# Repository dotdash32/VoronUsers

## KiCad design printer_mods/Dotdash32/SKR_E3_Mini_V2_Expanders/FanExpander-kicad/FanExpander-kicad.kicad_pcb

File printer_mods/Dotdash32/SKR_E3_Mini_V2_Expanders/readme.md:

# SKR E3 Mini V2.0 Expanders

A set of simple expander PCBs to give more thermistor and MOSFET fan outputs.

## Fan Expander

All fans have a 2 way voltage select header, and by moving a jumper between 5V and 24V (keeping the center Fx pin common), the drive voltage of the fan can easily be chosen.  If another voltage is desired for an individual fan, a jumper wire can also be tied directly into the Fx (center pin), providing any voltage higher than 5v.  All fans are broken out through JST-XH connectors.

All fans are also equipped with an indicator LED.  This LED is always driven from the 5V supply (EXP or external 5V supply pins) to ensure consistent brightness.  If you don't want the indicator LEDs, the jumper LED_EN can be cut to disable their power rail.  In a similar vein, if any fan is to be powered by less than 5V, the LED **must** be disabled at least for that fan, but is simplest to disable for the entire board by desoldering LED_EN.  

To keep all SMD components on one side (for manufacturing considerations), the LEDs shine through the board and into the connectors themselves.  This limits LED color options, but keeps the overall complexity and board size low.

### Fan Expander (Big Beefy Boi)

The "beefy boi" version of the Fan Expander uses either the EXP1 or EXP2 headers to drive up to 7 new fans and switch the voltage of one passthrough fan.  It can work next to a Thermistor Expander, or be mounted elsewhere and connected with a ribbon cable.

There are several "modes" of operation, mainly concerning voltage sources.  5V supply can come from the EXP header (EXP1 only), the 2 pin 5V header, or screw terminals.  24V (or other high voltage supply) can come from Fan0 In (passthrough fan) or the screw terminals.  Both supply lines are fused with ATM fuses, 3A standard, 10A optional.  See the [Operational_Modes.md](Operational_Modes.md) for detailed operation.

In general, JST-XH connectors are rated for 3A, and the BOM jumpers are specified to meet that current rating for each individual fan.  However, if using the Fan0 In connector, this limits the total current rating of the board.  Consider using the screw terminals for larger loads!

### Fan Expander Lite

The "Lite" version of the Fan Expander uses the EXP1 Header to drive 3 new fans and change the drive voltage for Fan1.  It is designed to be used next to the Thermistor Expander.  It is designed specifically for an SKR E3 in a Voron V0 (no external display, no SD card used).

Designed as a simpler, drop in solution than the fully featured Beefy Boi, it only has the LED_EN jumper and no others.  5V is supplied through EXP1, and 24V (or printer bus voltage) through Fan1 In connector.  Since it only uses 3 of 7 available I/O lines, so the remaining 4 lines are broken out to J7 IO Passthrough, next to a ground line each.

## Thermistor Expander

Uses SPI1 interface to add up to 3 thermistors on E3 based boards when an SD card is not needed.

Be aware, the SPI pins use 10k pull ups (next to SD-card on SKR board), which are different than the typical 4.7k pull ups.  This changes the thermistor sensitivity, so be aware they might not be as sensitive at printing temperatures.  This is based on Timmit's Umbilical mod, and the thermistor ports are designed for chamber and other low temperature and non-sensitive applications.

The TH4 Solder jumper switches the SPI pins that have been rearranged (V2.0 versus V3.0), and this solder jumper allows either SKR Mini E3 board to support 3 thermistors. All the pins are rearranged, so please see software configuration/schematic PDF for the correct pins for your board.

Klipper may try to read the SD card (which will fail, adding an RC circuit will destroy SPI timing requirements) during boot up if the thermistor pins are not declared as analog inputs, overriding their original SPI purpose.  Thus, please include the Thermistor Expander configuration before plugging the PCB in.  If your SKR refuses to boot, please unplug the Thermistor Expander PCB, boot up normally, then add the configuration file.

Requires 3 0805 SMD capacitors on the reverse side, which easier to source than THT variants (chip shortage, whoo), but are large enough to be relatively easy to hand solder.

## Bill of Materials

The BOM is shared between all sub-boards to make bulk ordering easier.

See the [Google Sheet](https://docs.google.com/spreadsheets/d/1q3EhH6Y6PAZSyFnE2HCBAoWyKbX_h1eaZGjsf7-CNqc/edit?usp=sharing).  Included is a "Composite Orderer" to allow a group order of all 3 sub assemblies to be ordered as one, as well as detailed BOMs for each.  This includes DigiKey alternatives to LCSC part numbers.

Each sub-project also has a csv file of it's specific BOM ready for import to LCSC included in this repository.  In each, JST-crimp connectors are also included, but can be excluded (since the larger wire gauge ones are sometimes difficult to source).  This saves some cost, but it's relatively small in the grand scheme of things.

## Errata

See the [Errata](Errata.md) for production issues and fixes.  While unfortunate, they must be documented.

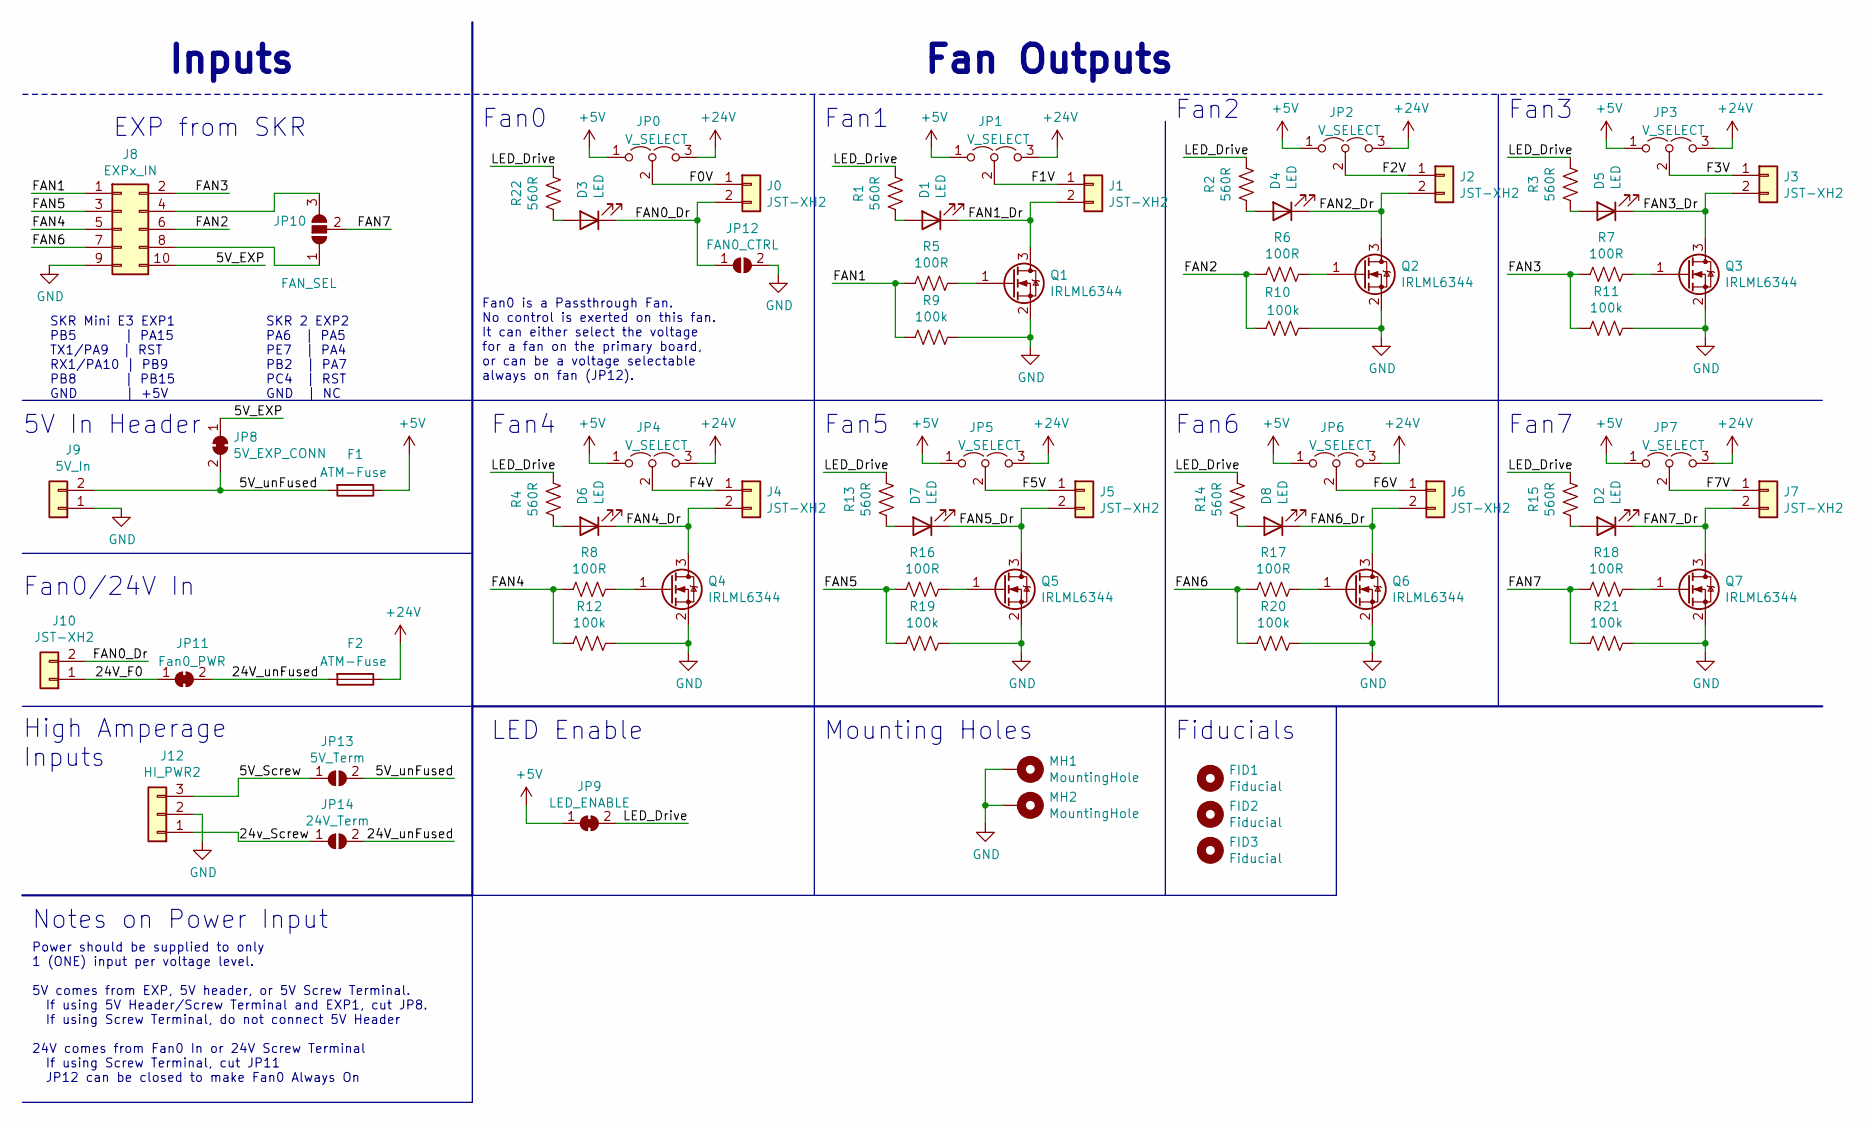
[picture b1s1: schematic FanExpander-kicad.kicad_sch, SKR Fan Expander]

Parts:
D1, D2, D3, D4, D5, D6, D7, D8: LED; LED_1206_3216Metric_ReverseMount_Hole2.1x2.1mm
F1, F2: ATM-Fuse; Fuseholder_Blade_Mini_Keystone_3544
FID1, FID2, FID3: Fiducial; Fiducial_0.5mm_Dia_1mm_Outer
J0, J1, J2, J3, J4, J5, J6, J7, J10: JST-XH2; JST_XH_B02B-XH-A_02x2.50mm_Straight
J8: EXPx_IN; Multicomp_MC9A12-1034_2x05x2.54mm_Straight
J9: 5V_In; Pin_Header_Straight_1x02_Pitch2.54mm
J12: HI_PWR2; TerminalBlock_Phoenix_MKDS-1,5-3-5.08_1x03_P5.08mm_Horizont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
JP0, JP1, JP2, JP3, JP4, JP5, JP6, JP7: V_SELECT; Pin_Header_Straight_1x03_Pitch2.54mm
JP8: 5V_EXP_CONN; SolderJumper-2_P1.3mm_Pasted_RoundedPad1.0x1.5mm
JP9: LED_ENABLE; SolderJumper-2_P1.3mm_Pasted_RoundedPad1.0x1.5mm
JP10: FAN_SEL; Pin_Header_Straight_1x03_Pitch1.27mm
JP11: Fan0_PWR; SolderJumper-2_P1.3mm_Pasted_RoundedPad1.0x1.5mm
JP12: FAN0_CTRL; SolderJumper-2_P1.3mm_Open_RoundedPad1.0x1.5mm
JP13: 5V_Term; SolderJumper-2_P1.3mm_Open_RoundedPad1.0x1.5mm
JP14: 24V_Term; SolderJumper-2_P1.3mm_Open_RoundedPad1.0x1.5mm
MH1, MH2: MountingHole; MountingHole_3.2mm_M3_Pad
Q1, Q2, Q3, Q4, Q5, Q6, Q7: IRLML6344; SOT-23
R1, R2, R3, R4, R13, R14, R15, R22: 560R; R_0603
R5, R6, R7, R8, R16, R17, R18: 100R; R_0603
R9, R10, R11, R12, R19, R20, R21: 100k; R_0603

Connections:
+5V: F1.1, JP0.1 (A), JP1.1 (A), JP2.1 (A), JP3.1 (A), JP4.1 (A), JP5.1 (A), JP6.1 (A), JP7.1 (A), JP9.1 (A)
+24V: F2.1, JP0.3 (B), JP1.3 (B), JP2.3 (B), JP3.3 (B), JP4.3 (B), JP5.3 (B), JP6.3 (B), JP7.3 (B)
/5V_EXP: J8.10, JP8.1 (A)
/5V_Screw: J12.3, JP13.1 (A)
/5V_unFused: F1.2, J9.2, JP8.2 (B), JP13.2 (B)
/24V_F0: J10.1, JP11.1 (A)
/24V_unFused: F2.2, JP11.2 (B), JP14.2 (B)
/24v_Screw: J12.1, JP14.1 (A)
/F0V: J0.1, JP0.2 (C)
/F1V: J1.1, JP1.2 (C)
/F2V: J2.1, JP2.2 (C)
/F3V: J3.1, JP3.2 (C)
/F4V: J4.1, JP4.2 (C)
/F5V: J5.1, JP5.2 (C)
/F6V: J6.1, JP6.2 (C)
/F7V: J7.1, JP7.2 (C)
/FAN0_Dr: D3.1 (K), J0.2, J10.2, JP12.1 (A)
/FAN1: J8.1, R5.2, R9.1
/FAN1_Dr: D1.1 (K), J1.2, Q1.3 (D)
/FAN2: J8.6, R6.2, R10.1
/FAN2_Dr: D4.1 (K), J2.2, Q2.3 (D)
/FAN3: J8.2, R7.2, R11.2
/FAN3_Dr: D5.1 (K), J3.2, Q3.3 (D)
/FAN4: J8.5, R8.2, R12.2
/FAN4_Dr: D6.1 (K), J4.2, Q4.3 (D)
/FAN5: J8.3, R16.2, R19.2
/FAN5_Dr: D7.1 (K), J5.2, Q5.3 (D)
/FAN6: J8.7, R17.2, R20.1
/FAN6_Dr: D8.1 (K), J6.2, Q6.3 (D)
/FAN7: JP10.2 (C), R18.2, R21.1
/FAN7_Dr: D2.1 (K), J7.2, Q7.3 (D)
/LED_Drive: JP9.2 (B), R1.2, R2.2, R3.2, R4.2, R13.2, R14.2, R15.2, R22.2
GND: J8.9, J9.1, J12.2, JP12.2 (B), MH1.1, MH2.1, Q1.2 (S), Q2.2 (S), Q3.2 (S), Q4.2 (S), Q5.2 (S), Q6.2 (S), Q7.2 (S), R9.2, R10.2, R11.1, R12.1, R19.1, R20.2, R21.2
unnamed: D1.2 (A), R1.1
unnamed: D2.2 (A), R15.1
unnamed: D3.2 (A), R22.1
unnamed: D4.2 (A), R2.1
unnamed: D5.2 (A), R3.1
unnamed: D6.2 (A), R4.1
unnamed: D7.2 (A), R13.1
unnamed: D8.2 (A), R14.1
unnamed: J8.4, JP10.3 (B)
unnamed: J8.8, JP10.1 (A)
unnamed: Q1.1 (G), R5.1
unnamed: Q2.1 (G), R6.1
unnamed: Q3.1 (G), R7.1
unnamed: Q4.1 (G), R8.1
unnamed: Q5.1 (G), R16.1
unnamed: Q6.1 (G), R17.1
unnamed: Q7.1 (G), R18.1

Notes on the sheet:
EXP from SKR
Fan1
Fan0 is a Passthrough Fan. No control is exerted on this fan. It can either select the voltage for a fan on the primary board, or can be a voltage selectable always on fan (JP12).
Fan0/24V In
Fan7
5V In Header
SKR 2 EXP2 PA6 | PA5 PE7 | PA4 PB2 | PA7 PC4 | RST GND | NC
Fan5
Mounting Holes
Notes on Power Input
Fan Outputs
LED Enable
Fan3
Fiducials
Fan0
SKR Mini E3 EXP1 PB5 | PA15 TX1/PA9 | RST RX1/PA10 | PB9 PB8 | PB15 GND | +5V
High Amperage Inputs
Fan4
Inputs
Fan6
Fan2
Power should be supplied to only 1 (ONE) input per voltage level. 5V comes from EXP, 5V header, or 5V Screw Terminal. If using 5V Header/Screw Terminal and EXP1, cut JP8. If using Screw Terminal, do not connect 5V Header 24V comes from Fan0 In or 24V Screw Terminal If using Screw Terminal, cut JP11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

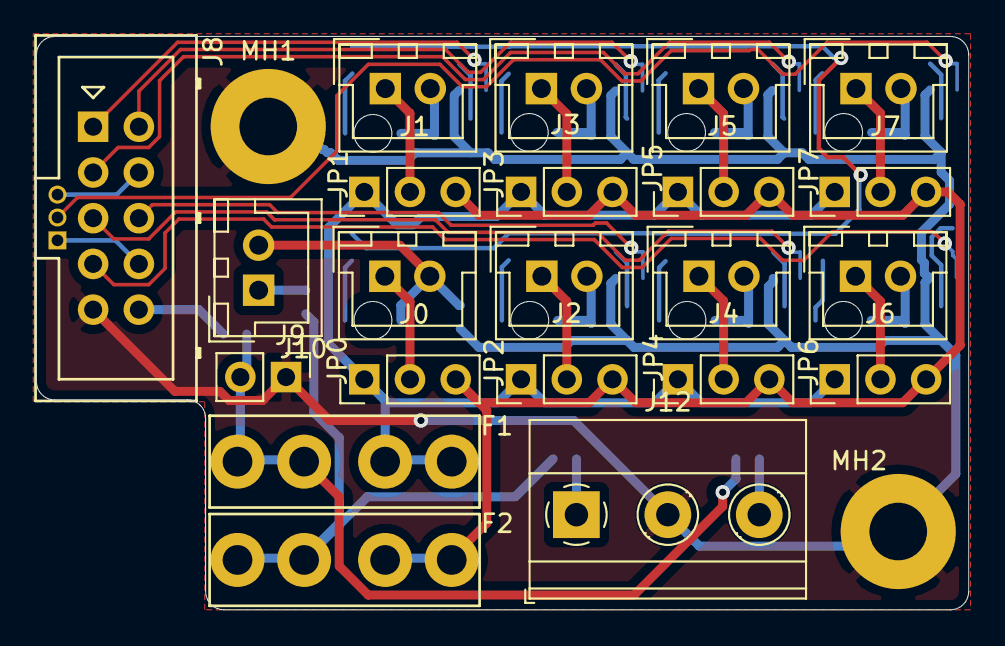
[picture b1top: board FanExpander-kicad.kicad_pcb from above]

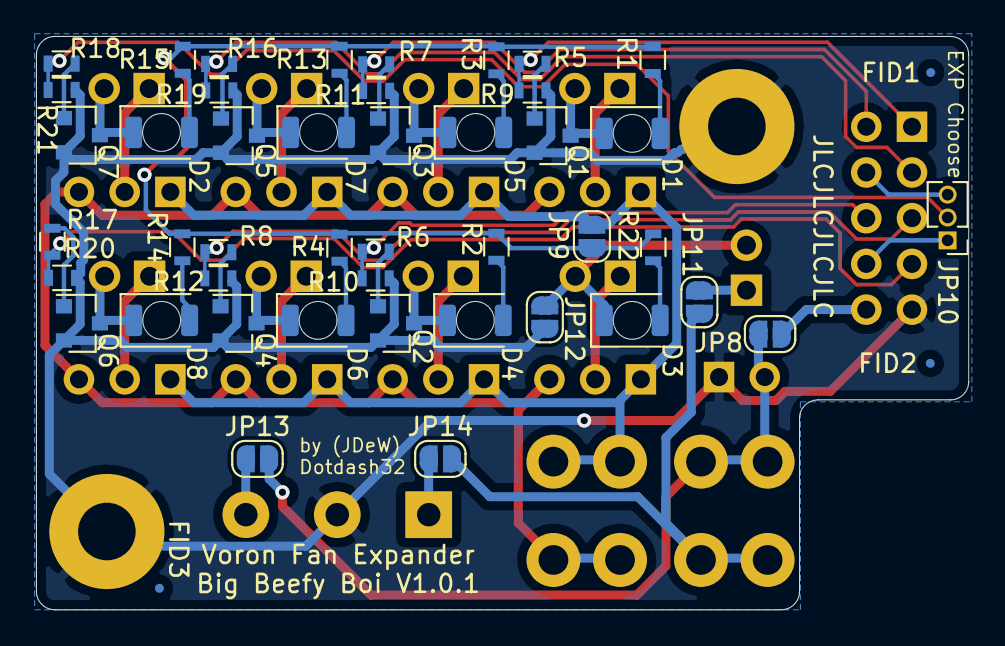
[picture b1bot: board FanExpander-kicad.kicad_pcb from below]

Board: 2 copper layers, 51.8 x 31.9 mm, 71 parts (47 on the bottom side), 50 nets.

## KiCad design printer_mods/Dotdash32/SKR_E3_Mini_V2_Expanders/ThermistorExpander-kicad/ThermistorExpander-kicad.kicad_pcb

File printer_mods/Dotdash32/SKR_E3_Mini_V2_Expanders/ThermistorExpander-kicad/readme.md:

# Thermistor Expander

This PCB is probably not supremely useful, but it has a special place in my heart.

Here are some pretty pictures of what it looks like!

## Images

### Bill of Materials

See the Google Doc linked on the main page

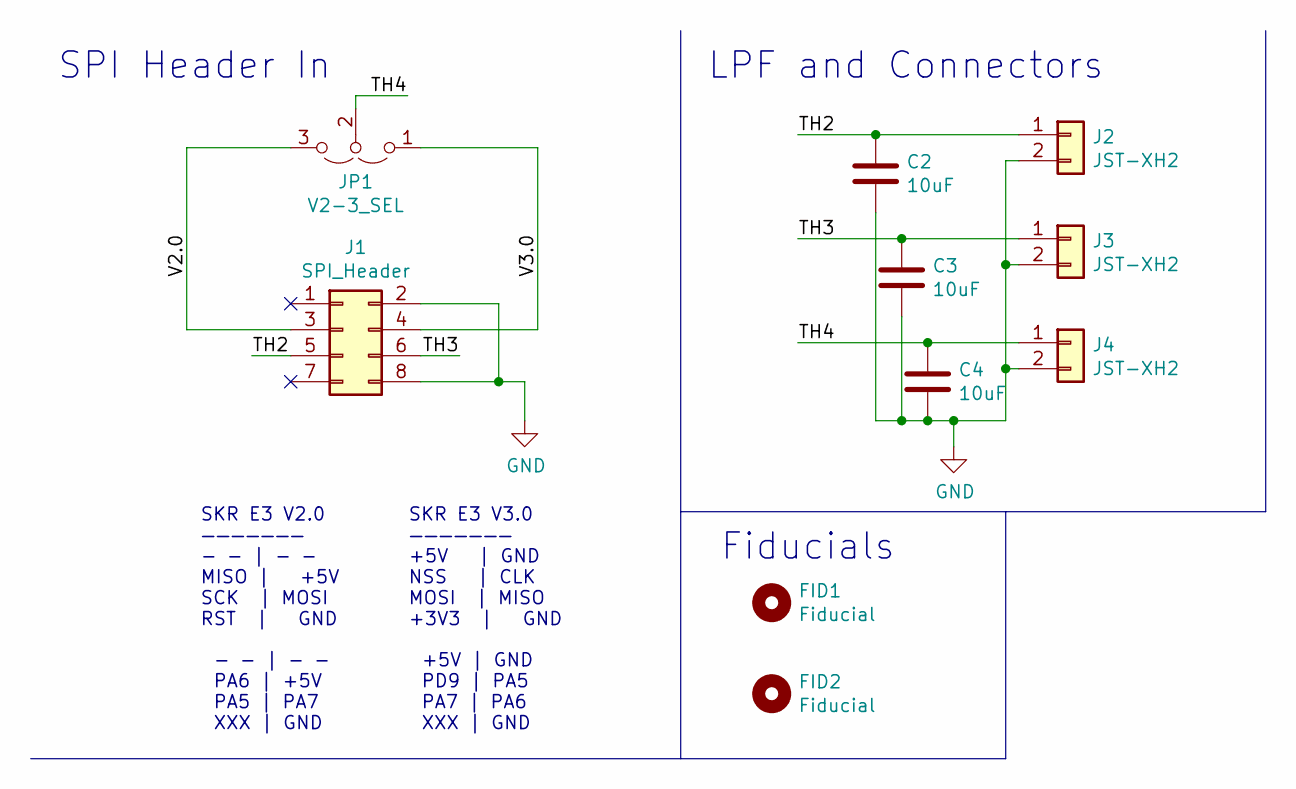
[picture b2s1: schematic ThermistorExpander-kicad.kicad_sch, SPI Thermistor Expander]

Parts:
C2, C3, C4: 10uF; C_0805_HandSoldering
FID1, FID2: Fiducial; Fiducial_0.5mm_Dia_1mm_Outer
J1: SPI_Header; Pin_Header_Straight_2x04_Pitch2.54mm
J2, J3, J4: JST-XH2; JST_XH_B02B-XH-A_02x2.50mm_Straight
JP1: V2-3_SEL; SolderJumper-3_P1.3mm_Open_Pad1.0x1.5mm

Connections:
/TH2: C2.1, J1.5, J2.1
/TH3: C3.1, J1.6, J3.1
/TH4: C4.1, J4.1, JP1.2 (C)
/V2.0: J1.3, JP1.3 (B)
/V3.0: J1.4, JP1.1 (A)
GND: C2.2, C3.2, C4.2, J1.2, J1.8, J2.2, J3.2, J4.2

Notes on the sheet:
- - | - - PA6 | +5V PA5 | PA7 XXX | GND
SPI Header In
LPF and Connectors
SKR E3 V2.0 ——————— - - | - - MISO | +5V SCK | MOSI RST | GND
Fiducials
+5V | GND PD9 | PA5 PA7 | PA6 XXX | GND
SKR E3 V3.0 ——————— +5V | GND NSS | CLK MOSI | MISO +3V3 | GND

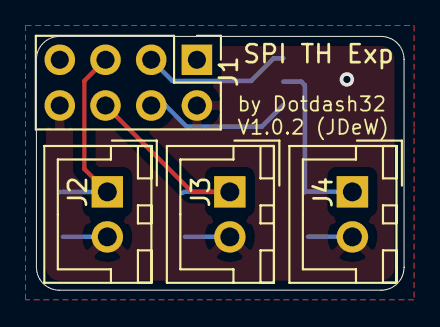
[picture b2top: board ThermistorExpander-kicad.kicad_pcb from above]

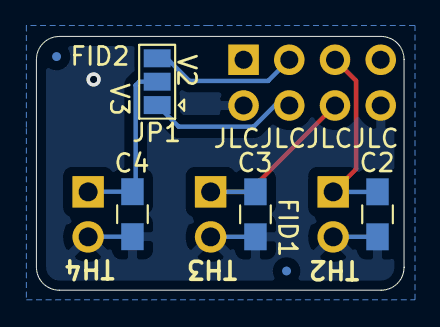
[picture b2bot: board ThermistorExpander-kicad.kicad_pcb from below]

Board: 2 copper layers, 20.4 x 14.1 mm, 10 parts (6 on the bottom side), 6 nets.

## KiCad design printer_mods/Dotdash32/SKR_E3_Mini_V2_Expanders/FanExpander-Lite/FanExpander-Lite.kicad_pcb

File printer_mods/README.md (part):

# Mods

Printer mods for Voron 3D printers
Remember to update this README when uploading new mod!

## Legacy printers

Mods for legacy printers can be found [here](../legacy_printers/printer_mods).
If one of your mods applies to a current generation Voron printer, contact the admins in
Discord to have your mod moved to this folder.

## Table structure

Update the following table with the information about your mod:
- Your name
- A link to your sub-folder
- A short description of your mod
- The printer compatibility. Use `:heavy_check_mark:` for :heavy_check_mark:,`:x:` for :x: and `:grey_question:` for :grey_question:

like so:
`
| Creator | [Mod title](link) | Description | :x: | :x: | :x: | :x: | :x:|`

---

| Creator | Mod title | Description | V0 | V1.8 | V2.4 | VSW | Trident |
| --- | --- | --- | --- | --- | --- | --- | --- |
|120decibell|[Side entry exhaust housing](./120decibell/exhaust_housing_side_entry)| Exhaust housing with dual cover screws and single or dual side entry filament paths. |:x:|:heavy_check_mark:|:heavy_check_mark:|:x:|:heavy_check_mark:|
||[Huvud Chain Mount](./120decibell/huvud_chain_mount)| Huvud rear mount for Clockwork or LGX that supports a cable chain. |:x:|:heavy_check_mark:|:grey_question:|:x:|:heavy_check_mark:|
|42bios|[Corner panel clip w. cable](./42bios/corner_panel_clip_cable)| Corner panel clip with an internal cable path. |:x:|:grey_question:|:heavy_check_mark:|:x:|
| |[Exhaust filter housing - side thread](./42bios/exhaust_filter_housing_side)|Exhaust filter housing with the G1-8 "thread on the side. |:x:|:grey_question:|:heavy_check_mark:|:x:|
| |[LED mount](./42bios/LED_mount)|AngryLED - LED-mount for Lumentech LT3 profiles. |:x:|:grey_question:|:heavy_check_mark:|:x:|
| |[relay mount](./42bios/relay_mount)|relay-mount for 2x 2 channel relay modules.|:x:|:grey_question:|:heavy_check_mark:|:x:|
|aeresov|[TL filament sensor bracket](./aeresov/TL_filament_sensor_bracket)|A bracket for TL filament sensor to mount near stock spool holder. |:x:|:grey_question:|:heavy_check_mark:|:x:|
||[MeanWell UHP-xxx DIN mount](./aeresov/MeanWell_UHP_DIN_mount)|A bracket for MeanWell UHP series PSU (200, 350 and 500) to mount it across 2 DIN rails.|:x:|:grey_question:|:heavy_check_mark:|
||[Raspberry Pi DIN mount](./aeresov/Raspberry_Pi_DIN_mount)|A bracket for Raspberry Pi 3/4 to mount it onto DIN rail, along or across.|:x:|:grey_question:|:heavy_check_mark:|
||[SKR 1.3/1.4 DIN mount](./aeresov/SKR_DIN_mount)|A bracket for SKR 1.3/1.4 board to mount it onto DIN rail, along or across.|:x:|:grey_question:|:heavy_check_mark:|
||[cable tie DIN mount](./aeresov/cable_tie_DIN_mount)|A bracket for cable ties to route cables across DIN rails.|:x:|:grey_question:|:heavy_check_mark:|
|alanho|[BTT PITFT50 v2 Mount](./alanho/BTT_PITFT50_v2_Mount)|A mount for the BTT PITFT50 v2 Touch Display |:x:|:grey_question:|:heavy_check_mark:|:x:|
|albert|[IKEA Dioder Led Mount](./albert/IKEA_Dioder_Led_Mount)|A mount for the IKEA Dioder LED strip | :grey_question: | :grey_question: | :heavy_check_mark: |:x:|
|al3ph|[LED Mount](./al3ph/led_mount)|A mount for 10mm LED WS2812 strips |:heavy_check_mark:|:x:|:x:|:x:|
| |[Analog Timer Mount](./al3ph/analog_timer_mount)|A skirt mount for analog timer |:heavy_check_mark:|:x:|:x:|:x:|
| |[Filament Runout Sensor](./al3ph/filament_runout)|A simple filament runout sensor |:heavy_check_mark:|:heavy_check_mark:|:heavy_check_mark:|:heavy_check_mark:|
| |[PL05 Sensor Mount](./al3ph/pl05_mount)|A mount PL05 inductive sensor |:heavy_check_mark:|:x:|:x:|:x:|
|Andre|[Mini Afterburner Strain Relief](./Andre/Mini_Afterburner_Strain_Relief)|A replacement strain relief for the Mini Afterburner toolhead|:heavy_check_mark:|:x:|:x:|:x:|
| |[V0 Neopixel Front Bed Mount](./Andre/V0_Neopixel_Front_Bed_Mount)|A replacement Front Bed Mount with room for a neopixel or dotstar behind the logo|:heavy_check_mark:|:x:|:x:|:x:|
| |[Mini Afterburner ADXL345 Mount](./Andre/Mini_Afterburner_ADXL345_Mount)|Mount for an AXDL345 on the Mini Afterburner|:heavy_check_mark:|:x:|:x:|:x:|
|arkeet|[Dial test indicator mount](./arkeet/dti-mount)|A toolhead mount for a dial test indicator, where the tip is located at the nozzle. |:x:|:heavy_check_mark:|:heavy_check_mark:|:x:|
| |[Magnetic hotend fan cover](./arkeet/magnet-fan-cover)|A replacement hotend fan cover, held with magnets instead of screws. |:x:|:heavy_check_mark:|:heavy_check_mark:|:heavy_check_mark:|
| |[MGN12 X-axis](./arkeet/mgn12/)|Replaces the dual MGN9H rails with a single MGN12H. |:x:|:x:|:heavy_check_mark:|:x:|
| |[V0 DC inlet](./arkeet/v0-dc-inlet/)|Skirt inlet for external 24V DC power supply. |:heavy_check_mark:|:x:|:x:|:x:|
|Badnoob |[Precision AB Drive](./Badnoob/Precision_AB_Drive)|Changes the gearing for the AB drives to improve both resolution and torque, with a strenthened frame. |:grey_question:|:grey_question:|:heavy_check_mark:|:x:|
| |[AB-BN Afterburner mod (5015)](./Badnoob/AB-BN)|Improved Afterburner with 5015 fan |:x:|:heavy_check_mark:|:heavy_check_mark:|:heavy_check_mark:|:heavy_check_mark:|
| |[AB-BN for Stock Afterburner (4020)](./Badnoob/ABBN_for_Stock)|Improved Dragon and Rapido toolhead for stock Afterburner with 4020 fan |:x:|:heavy_check_mark:|:heavy_check_mark:|:heavy_check_mark:|:heavy_check_mark:|
| |[Rail Alignment](./Badnoob/Rail_Alignment)|Tools and procedure to properly align the rails in 2.4 and Afterburner|:x:|:x:|:heavy_check_mark:|:x:|
|Baltojikale | [LoudOwl aka Stabby](./Baltojikale/LoudOwl_aka_Stabby) | Alternative dual 5015 part cooling fan toolhead for Afterburner | :x: | :heavy_check_mark: | :heavy_check_mark: | :heavy_check_mark: |
|beaugalbraith| [Nova Printhead](./beaugalbraith/Nova_Printhead) | Use Nova Hotend with Afterburner | :grey_question: | :grey_question: | :heavy_check_mark: | :grey_question: | :grey_question:|
| BladeScraper-Designs | [Microswitch Pod With Connector](./BladeScraper-Designs/Microswitch_Pod_With_Conector) | Microswitch pod with JST-XH 4-pin connector | :x: |:x: |:heavy_check_mark: | :x:
| | [Horizontal Spool Holder](./BladeScraper-Designs/Horizontal-Spool-Holder) | Based on the stock holder but mounts to the horizontal extrusions. | :x: | :grey_question: |:heavy_check_mark: | :grey_question:
|Blamm|[LRS-100 DIN mount](./Blamm/lrs-100)|DIN rail mount for an extra LRS-100 Power Supply | :x: | :heavy_check_mark: | :heavy_check_mark: |:grey_question:| :heavy_check_mark:|
|BlueBear|[Deck Panel Backpack](./BlueBear/Deck_Panel_Backpack)|A mounting alternative if you don't want to drill your deck panel | :heavy_check_mark: | :x: | :x: |:x:|
||[Clippable Wago 221 Mounts](./BlueBear/Wago_221_mount)|Mounts for Wago 221 to screw or clip-in on 1515 extrusions | :heavy_check_mark: | :x: | :x: |
||[Ziptie Mount](./BlueBear/Ziptie_Mount)|Clippable Ziptie hooks for 1515 extrusions| :heavy_check_mark: | :x: | :x: |
| bobbleheed | [Magnetic Panels](./bobbleheed/Magnetic_Panels) | Magnetic clips to allow for easy removal and installation of panels | :x: | :grey_question: | :heavy_check_mark: | :x: | :grey_question: |
| | [Filament Runout Sensor](./bobbleheed/Filament_Runout) | Filament runout sensor that replaces the stock bowden retainer | :x: | :heavy_check_mark: |:heavy_check_mark: | :x: | :heavy_check_mark: |
|Boingomw|[Wago mount](./Boingomw/Wago_mount)| Smaller 5 port Wago mount that fits parallel to the support rails |:x:|:grey_question:|:heavy_check_mark:|:x:|:grey_question:|
| btp | [Galileo chain mount (befenybay)](./btp/Galileo_Switchwire_Chain_Mount/README.md) | Modified chain mount position to cater for difference with Galileo Clockwork |:x:|:x:|:x:|:heavy_check_mark:|
| buzzdalf | [v1.8/2.4 Afterburner connector cover for 42STH20-1004AS](./buzzdalf/connector_cover) | v1.8/2.4 Connector cover for 42STH20-1004AS | :x: | :heavy_check_mark: | :heavy_check_mark: |:grey_question:|
||[Ender 3 Switchwire Taller Z Mod](./buzzdalf/ender_switchwire_taller_z) | Taller Z Mod | :x: | :x: | :x: | :heavy_check_mark: |
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
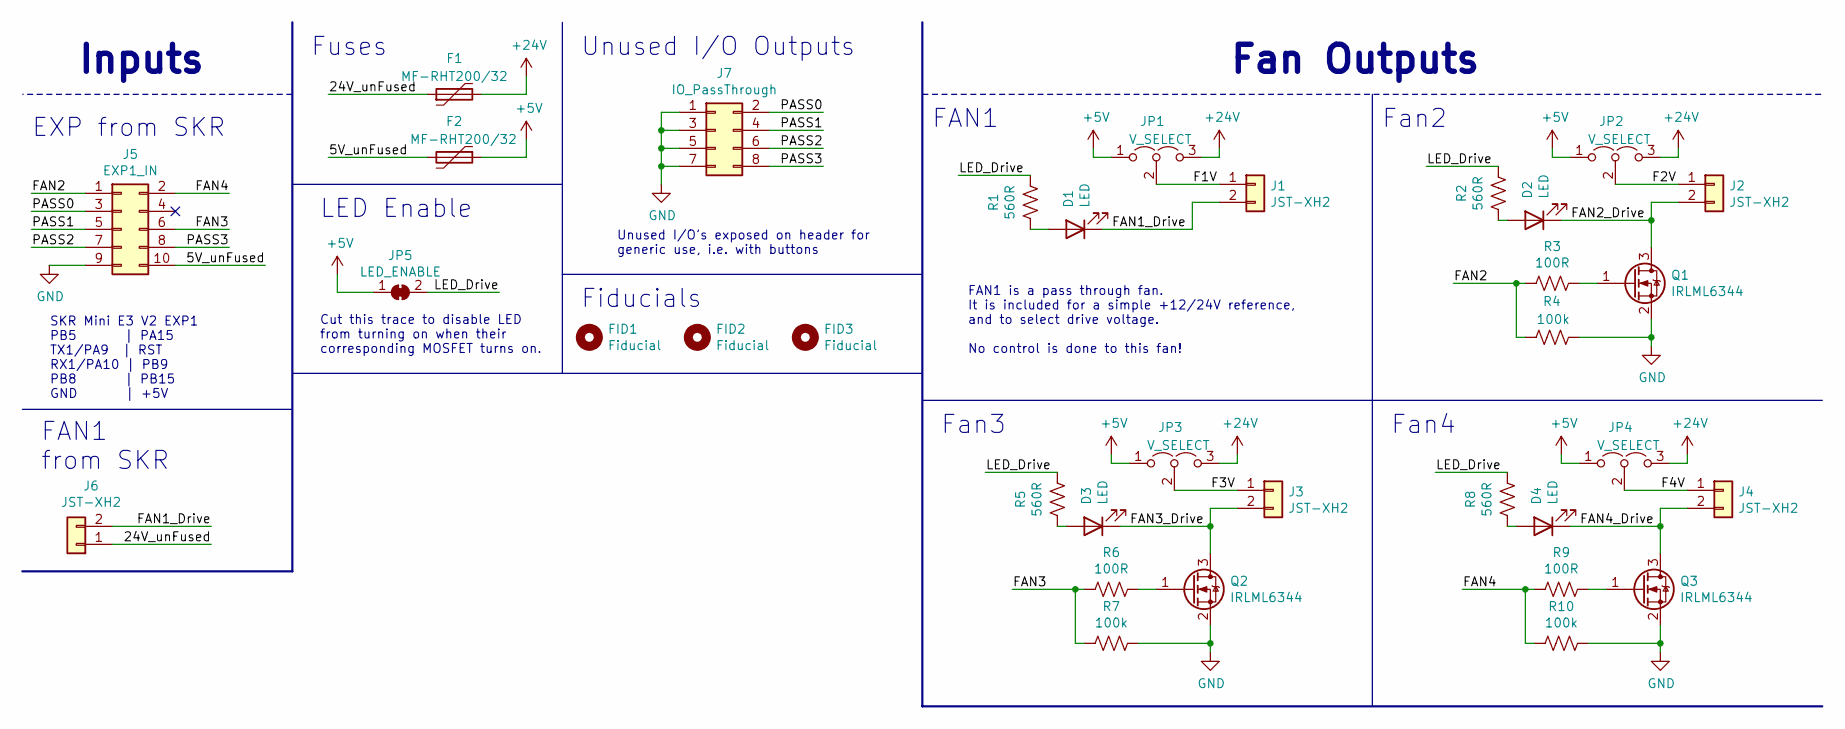
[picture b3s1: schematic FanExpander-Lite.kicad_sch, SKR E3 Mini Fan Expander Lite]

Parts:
D1, D2, D3, D4: LED; LED_1206_3216Metric_ReverseMount_Hole2.1x2.1mm
F1, F2: MF-RHT200/32; Fuse_Bourns_MF-RHT200
FID1, FID2, FID3: Fiducial; Fiducial_0.5mm_Dia_1mm_Outer
J1, J2, J3, J4, J6: JST-XH2; JST_XH_B02B-XH-A_02x2.50mm_Straight
J5: EXP1_IN; Multicomp_MC9A12-1034_2x05x2.54mm_Straight
J7: IO_PassThrough; Pin_Header_Straight_2x04_Pitch2.54mm
JP1, JP2, JP3, JP4: V_SELECT; Pin_Header_Straight_1x03_Pitch2.54mm
JP5: LED_ENABLE; SolderJumper-2_P1.3mm_Pasted_RoundedPad1.0x1.5mm
Q1, Q2, Q3: IRLML6344; SOT-23
R1, R2, R5, R8: 560R; R_0603
R3, R6, R9: 100R; R_0603
R4, R7, R10: 100k; R_0603

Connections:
+5V: F2.1, JP1.1 (A), JP2.1 (A), JP3.1 (A), JP4.1 (A), JP5.1 (A)
+24V: F1.2, JP1.3 (B), JP2.3 (B), JP3.3 (B), JP4.3 (B)
/5V_unFused: F2.2, J5.10
/24V_unFused: F1.1, J6.1
/F1V: J1.1, JP1.2 (C)
/F2V: J2.1, JP2.2 (C)
/F3V: J3.1, JP3.2 (C)
/F4V: J4.1, JP4.2 (C)
/FAN1_Drive: D1.1 (K), J1.2, J6.2
/FAN2: J5.1, R3.2, R4.1
/FAN2_Drive: D2.1 (K), J2.2, Q1.3 (D)
/FAN3: J5.6, R6.2, R7.2
/FAN3_Drive: D3.1 (K), J3.2, Q2.3 (D)
/FAN4: J5.2, R9.2, R10.2
/FAN4_Drive: D4.1 (K), J4.2, Q3.3 (D)
/LED_Drive: JP5.2 (B), R1.2, R2.2, R5.2, R8.2
/PASS0: J5.3, J7.2
/PASS1: J5.5, J7.4
/PASS2: J5.7, J7.6
/PASS3: J5.8, J7.8
GND: J5.9, J7.1, J7.3, J7.5, J7.7, Q1.2 (S), Q2.2 (S), Q3.2 (S), R4.2, R7.1, R10.1
unnamed: D1.2 (A), R1.1
unnamed: D2.2 (A), R2.1
unnamed: D3.2 (A), R5.1
unnamed: D4.2 (A), R8.1
unnamed: Q1.1 (G), R3.1
unnamed: Q2.1 (G), R6.1
unnamed: Q3.1 (G), R9.1

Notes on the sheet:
Fan4
SKR Mini E3 V2 EXP1 PB5 | PA15 TX1/PA9 | RST RX1/PA10 | PB9 PB8 | PB15 GND | +5V
Fan3
Fan Outputs
LED Enable
EXP from SKR
Fiducials
Inputs
FAN1 from SKR
FAN1
FAN1 is a pass through fan. It is included for a simple +12/24V reference, and to select drive voltage. No control is done to this fan!
Unused I/O Outputs
Fan2
Fuses
Cut this trace to disable LED from turning on when their corresponding MOSFET turns on.
Unused I/O’s exposed on header for generic use, i.e. with buttons

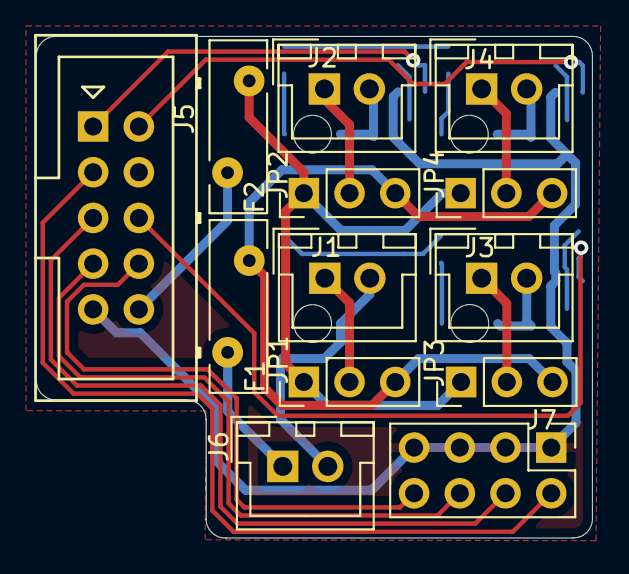
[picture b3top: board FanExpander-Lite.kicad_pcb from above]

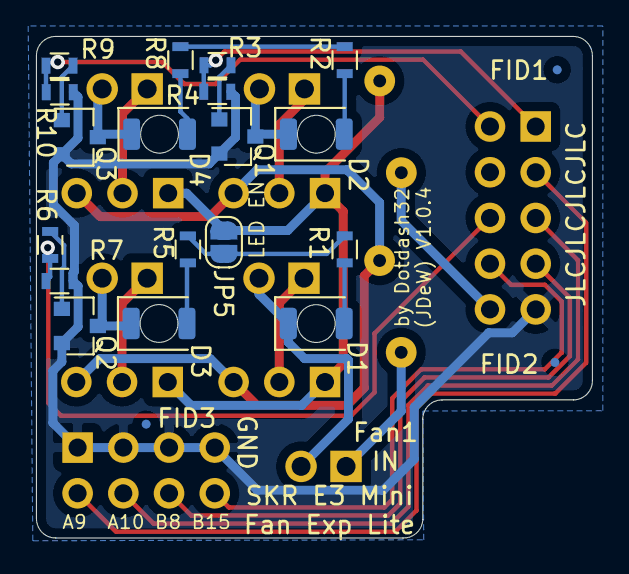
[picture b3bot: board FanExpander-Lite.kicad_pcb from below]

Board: 2 copper layers, 30.9 x 27.9 mm, 34 parts (21 on the bottom side), 28 nets.

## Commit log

2021-11-23 feat: add X endstop bumper Mod STL
2021-11-23 docs: add images and more explanation
2021-11-23 chore: add full source files with assembly contexts
2021-11-23 docs: add table entry to main mods readme
2021-11-23 fix: mis-capitalized image
2021-11-23 fix: typo in url to subfolder
2021-11-25 feat: add Z endstop embiggener, materials needed
2021-11-25 docs: create readme for iNtEnTiOn
2021-11-25 feat: thermistor expander schematic
2021-11-26 feat: fan expander PCB
2021-11-27 chore: change fan2 and 3 numbering
2021-11-29 docs: create Andon folder/readme
2021-11-29 feat: initial andon with base toggle feature
2021-11-29 feat: expose LED to UI, but intercept color cmds
2021-11-29 feat: startup test (blink in different colors)
2021-12-01 fix: move write_andon to SET_LED, more bugs
    now uses SET_LED MODE=internal to return led's to stored state,
    but running into some bugs.
    Also created an LED state machine, but doesn't reach the final state
    pushing to ask on Discord
2021-12-01 fix: state machine now completes
    it moves to an extra state that just repeats the last command,
    which is weird, but it seems to work?
2021-12-01 feat: array startup welcome (ty @VintageGriffin)
2021-12-01 style: remove unused state machine
2021-12-01 fix: move around parameter pull, now can toggle!
    one caveat: if you use the GUI color picker, you need to reslide the
    intensity/brightness slider up after a toggle Off.
    Annoying, but probably the standard cost \shrug
2021-12-01 refactor: move to arrays for color storage
    Again, VintageGriffin coming in clutch with some refactor changes.
    Uses a tuple (?) to store the three (or four I guess) RGBW values and
    cycle through them for startup.
    Also makes it more compact to store the data in our _andonvars macro
2021-12-13 test: LTspice circuit for varying pullup values
    examine the AC (cutoff frequency) and DC characteristics
    and affects of the standard thermistor pullup by changing the
    value of the pullup resistor.
    I never actually got around to graphing cutoff frequency as a function
    of temperature (which was the OG goal), but got some interesting
    data nonetheless.
2021-12-13 feat: create readme and upload init STL files
2021-12-13 docs: add images and materials list
2021-12-13 feat: add source fusion file
2021-12-14 docs: fixing typos in readme
2021-12-14 docs: I/O characteristic analysis for PC14
2021-12-15 feat: PCB init layout and 3d connector models
2021-12-17 feat: create .STEP export and first image
2021-12-17 feat: move JST headers to avoid EXP1 port
    but now interfering with the USB port, which is more useful.
    So maybe we try to use the vertical headers and admit defeat?
    sad bears, sad beers
2021-12-17 feat: use straight JSTs, clear existing SKR ports
2021-12-17 fix: actually route the traces please
2021-12-17 docs: information for TH EXP assembly, pics
2021-12-17 docs: LED leakage current analysis
2021-12-17 feat: new fan expander using EXP1 header
2021-12-18 chore: cleaning LTspice files
2021-12-18 feat: init footprints, rename connectors per use
2021-12-18 test: initial layout, trying different mosfet arrs
    testing different arragnments of Mosfets and associated
    hardware, seeing the best routing and labelling way.
    Trying to keep the designators on the board, which takes up space,
    but in general i think i need to make things more sparse.
2021-12-19 feat: no ADC in EXP1, add more fans!!!
2021-12-19 feat: create "Lite" Fan Expander with 3 MOSFETs
    it's smaller and more minimalistic. SMD polyfuses,
    no screw terminals, all JST connections.
    Probably not what Timmit99 had envisioned, but I think this is
    going to be easier to "sell".
2021-12-19 feat: init routing of Lite board
2021-12-19 chore: cleanup edges, silkscreen, making pretty
2021-12-19 docs: overview of FELite and operation
2021-12-22 feat: beefy expander sch cleaned, initial layout
    schematic looks good, but the layout needs work.
    RN, it covers too much, so needs to have the EXP header stick out
    a lot more than it already is, probably make the whole thing longer
2021-12-23 test: using 1xXX pins for breakaways?
2021-12-23 feat: breakaway layout, using 1mm spacing headers
    it works, but its SOOO LOOOONG, going to try again and make it
    more compact so I don't feel bad about this long stick in my printer
2021-12-24 feat: move SMD components to bottom for sizing
    this really messes with the designator cleanliness, but alas,
    sacrifices must be made. It's really smalll now!
    Also some schematic cleaning. Should there be a second set of
    mounting holes next to the connector? unclear...
2021-12-25 chore: trying routing, running into obstacles
    no room to route the control wires, everything else is *almost*
    there though.
2022-01-02 feat: re-routing, pre-terminal blocks
    A bunch of routing work, but i'm not fully happy with it, still.
    new plan is to mess around and add back the terminal blocks, as well
    as move back to full size ATM fuses.
2022-01-02 test: move to ATM fuses, keep breakaway
    I don't think the breakaway is actuall worthwhile??
2022-01-02 feat: new layout with screw terminals and jumpers
    add more jumpers to make any kind of voltage selection more easy,
    particularly for fan0, either always on or cutting 24V in
    no routing done yet lol
2022-01-02 feat: shrink TH_exp to be more space efficient
2022-01-02 chore: routing TH exp in new formfactor
2022-01-02 feat: redo layout to use backside SMD parts
    move to align with main board version, compactness!
    Also moving to larger THT PTC fuses
2022-01-04 feat: routing the board
    no external 5V tap, but it'll probably be fine??
2022-01-06 feat: add BOM files
2022-01-06 feat: trim outline to not collide with TH exp
    also some fun little changes for internal structure
2022-01-06 chore: proper saving proceedure
2022-01-08 feat: cleaning and preping TH expander
2022-01-09 feat|docs: 2x4 SPI header, readme updates
    also re-routing some silly decisions, cleaning schematic
    Also moving some readme-stuff around for
2022-01-09 test: LCSC larger THT capacitor
    it's sooo bigg though...
2022-01-09 feat: move to SMD capacitors for sourcing
    upsetti spaghetti, THT capacitors are hard to find, so we'll just
    use SMD (1206) capacitors
2022-01-09 chore: create gerbers for TH exp v1.0
2022-01-10 chore|docs: create gerbers, update readme+images
    also got the bom working better, integrated with LCSC!
2022-01-10 feat: add LCSC bom, add alignment fiducials
    redoing some BOM stuff, oh how i hate BOM management
2022-01-10 feat: updating BOM, add fiducials
    JLCPCB 1206 caps are "discontinued" so moving to instock 0805
    capacitors. Updating BOM, creating LCSC importer
2022-01-11 fix: add JST housings and crimp connectors to BOMs
    crimp connecotrs alone are like 70c, which is like 20% of the BOM??
2022-01-11 chore: updating layout to new method, new LED
    new LED reverse mount footprint, should be slightly less bulky
    and make sure all the light just goes up through JST connector
2022-01-11 fix: update reverse LED mounts at SCH level
    were using the wrong hole pattern, not big enough!!
2022-01-11 fix: clean Diode references on PCB
2022-01-12 chore: changing values for BOM export
2022-01-12 feat: initial routing of FE beefy boi
2022-01-15 feat: pcb corner fillets, silk layout
2022-01-16 feat: prep big expander for release
2022-01-16 feat: solder paste filled jumpers
2022-01-16 feat: BOM for big fan expander
2022-02-01 chore|test: laser cut solder stencil tests
    .ai file did work, kapton tape stuck to itself and it applies paste pretty well!
2022-02-01 docs: top/bottom images, fuse holder STL
    running into an issue such that i can't export the STEP file of the
    entire system (for assembly jig), but we can find a workaround
    eventually, hopefully.
2022-02-02 docs: update Readme add Op Modes and Errata
    readme now has images and prose reads more clearly,
    less repetition.
    more detailed Operational Modes, and including errata of fuckups i made
2022-02-02 docs: assembly aid drawings, highlight which components go where
    pretty colors and labels for easier assembly stuff
2022-02-02 fix: PNs are for manufacturer, not LCSC
2022-02-04 chore: update to KiCad 6.0, better EXP 3D model
    move to KiCad 6 in order to export step files, lol.
    Also, improve the direct EXP1 plug in so it's more accurate to size
    add local .gitignore to ignore backup files
2022-02-04 chore: update Thermistor expander to KiCad 6
2022-02-10 docs: fix FEL version #, add LED backdrive errata
    gaaah, this backdrive is annoying. It's also an indicator that 5V
    is active on the board, but i don't really like that tbh...
2022-02-10 chore: update FE to Kicad 6, add resistor 3d comps
